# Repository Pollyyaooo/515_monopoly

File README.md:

# Smart Monopoly

A smart Monopoly system that automatically tracks board state and enforces rules, so players can focus on strategy and fun.

## Demo Videos

| Scenario | Link |
|---|---|
| Vision detection — green house | [Watch](https://drive.google.com/file/d/1YYkAQqQGW3G5yaRUnQ6ajyW9RlyFcLrm/view?usp=drive_link) |
| Vision detection — red hotel | [Watch](https://drive.google.com/file/d/1fPO76GP8kFQUbU6NWimg8kV7IUoyudl7/view?usp=drive_link) |
| Auction | [Watch](https://drive.google.com/file/d/1G2KbDcnRxIF2fS2yyap2P3zmI8cTID51/view?usp=drive_link) |
| NFC payment | [Watch](https://drive.google.com/file/d/1PzwGUXprhIAtn__mJcu651hlFBT1dVyA/view?usp=drive_link) |

## System Overview

The system consists of three main components:

- **Vision subsystem** — Grove Vision AI V2 detects house/hotel placement on the board. An ESP32-C3 processes the raw coordinates into property-level data and transmits it to the central bank via ESP-NOW.
- **Central bank** — CrowPanel ESP32 5" manages all public game logic (dice rolls, chance/community cards, auctions, jail) and syncs state to both player devices via BLE. It also receives vision data and alerts players if houses are placed incorrectly.
- **Player devices (×2)** — Each device (XIAO ESP32-S3) has an OLED display, 4 buttons, and an NFC reader. Players use buttons to interact with the game and tap devices together for rent payments and auctions.

## Repository Structure

```
515_monopoly/
├── README.md
├── assets/
│   ├── full_view.jpg
│   └── details.jpg
├── software/
│   ├── README.md               # Code running instructions
│   ├── central_bank/           # CrowPanel ESP32 game logic & display
│   ├── player_card/            # XIAO ESP32-S3 player device firmware
│   ├── vision/                 # Grove Vision AI V2 + ESP32-C3 (ESP-NOW sender)
│   ├── central_display_test/   # Display UI testing
│   └── player_device_test/     # Player device testing
├── hardware/
│   ├── playbox+vision.f3z      # Fusion 360 enclosure & camera mount
│   ├── playbox_lasercut/       # SVG files for laser cutting
│   ├── player_card.f3z         # Fusion 360 player card enclosure
│   ├── player_card_pcb/        # PCB design files
│   ├── player_card_model/      # Player card 3D model files
│   └── vision_archi/           # Vision module hardware files
├── docs/
│   ├── milestone1.pdf
│   ├── milestone2.pdf
│   └── milestone3.pdf
└── test/                       # Early-stage hardware experiments (abandoned)
    ├── RFID test/
    ├── Hall Effect test/
    └── FSR test/
```

## Hardware

| Component | Role |
|---|---|
| Grove Vision AI V2 | House / hotel detection |
| ESP32-C3 | Coordinate processing & ESP-NOW transmission |
| CrowPanel ESP32 5" | Central bank — game logic & public display |
| XIAO ESP32-S3 (×2) | Player devices |
| OLED SSD1351 (×2) | Player display |
| NFC reader (×2) | Rent payment between players |

## Communication

| Link | Protocol |
|---|---|
| Grove Vision AI V2 → ESP32-C3 | UART |
| ESP32-C3 → CrowPanel | ESP-NOW |
| CrowPanel ↔ Player devices | BLE |
| Player device ↔ Player device | NFC |

## Team

- **Sienna** — All software (except vision model training)
- **Polly** — All hardware (enclosure, PCB, player card), vision model training & grid calibration

## Legacy Test Code

The `test/` folder contains early-stage hardware experiments (RFID, Hall Effect, FSR) that were explored during Milestone 1 but later abandoned in favour of the vision-based detection approach.

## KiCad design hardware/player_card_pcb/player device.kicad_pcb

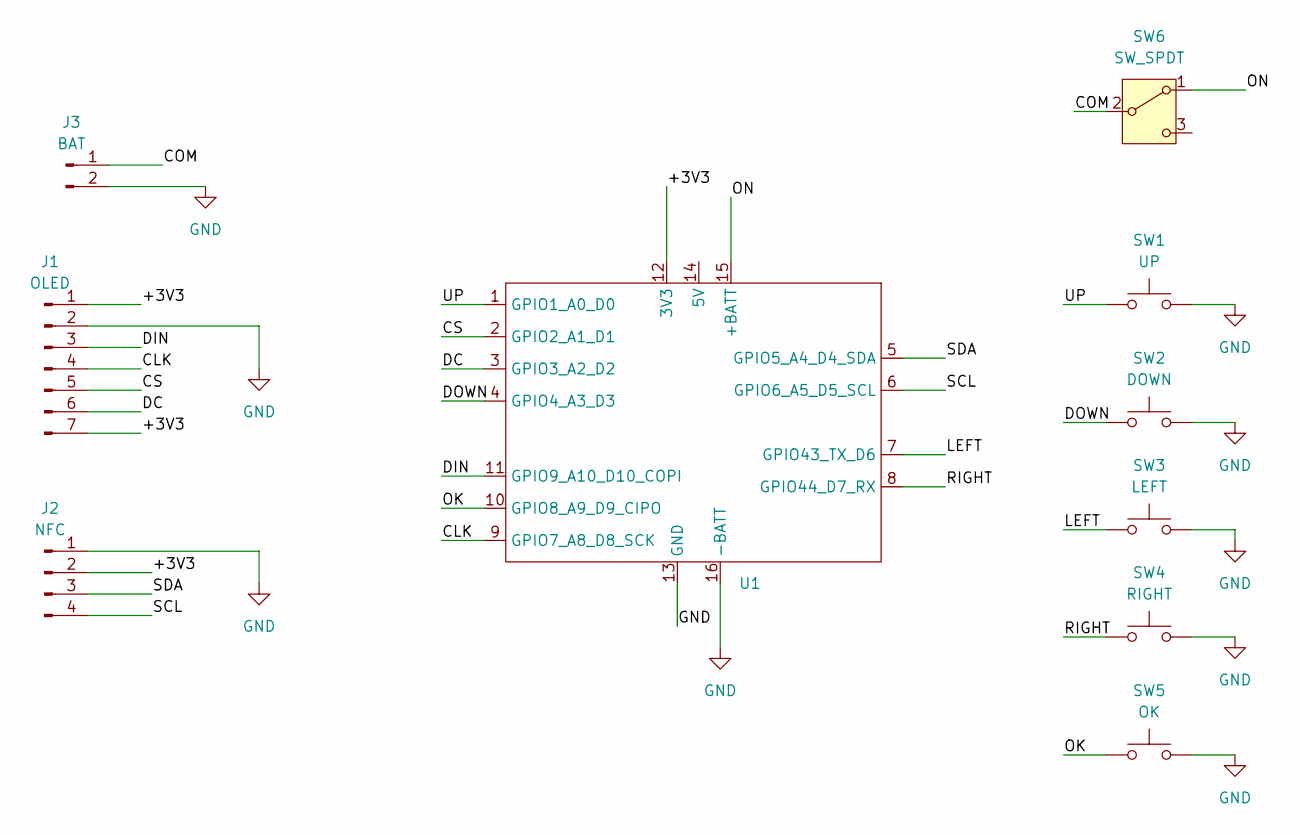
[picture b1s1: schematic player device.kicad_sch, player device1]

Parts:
J1: OLED; PinHeader_1x07_P2.54mm_Vertical
J2: NFC; PinHeader_1x04_P2.54mm_Vertical
J3: BAT; JST_SH_SM02B-SRSS-TB_1x02-1MP_P1.00mm_Horizontal
SW1: UP; SW_TS04-66-70-BK-260-SMT
SW2: DOWN; SW_TS04-66-70-BK-260-SMT
SW3: LEFT; SW_TS04-66-70-BK-260-SMT
SW4: RIGHT; SW_TS04-66-70-BK-260-SMT
SW5: OK; SW_TS04-66-70-BK-260-SMT
SW6: SW_SPDT; PinHeader_1x03_P2.54mm_Vertical
U1: XIAO_ESP32

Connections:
/+3V3: J1.1 (VCC), J1.7 (RST), J2.2 (VCC), U1.12 (3V3)
/CLK: J1.4 (CLK), U1.9 (GPIO7_A8_D8_SCK)
/COM: J3.1 (+), SW6.2 (B)
/CS: J1.5 (CS), U1.2 (GPIO2_A1_D1)
/DC: J1.6 (DC), U1.3 (GPIO3_A2_D2)
/DIN: J1.3 (DIN), U1.11 (GPIO9_A10_D10_COPI)
/DOWN: SW2.1, U1.4 (GPIO4_A3_D3)
/LEFT: SW3.1, U1.7 (GPIO43_TX_D6)
/OK: SW5.1, U1.10 (GPIO8_A9_D9_CIPO)
/ON: SW6.1 (A), U1.15 (+BATT)
/RIGHT: SW4.1, U1.8 (GPIO44_D7_RX)
/SCL: J2.4 (SCL), U1.6 (GPIO6_A5_D5_SCL)
/SDA: J2.3 (SDA), U1.5 (GPIO5_A4_D4_SDA)
/UP: SW1.1, U1.1 (GPIO1_A0_D0)
GND: J1.2 (GND), J2.1 (GND), J3.2 (-), SW1.2, SW2.2, SW3.2, SW4.2, SW5.2, U1.13 (GND), U1.16 (-BATT)

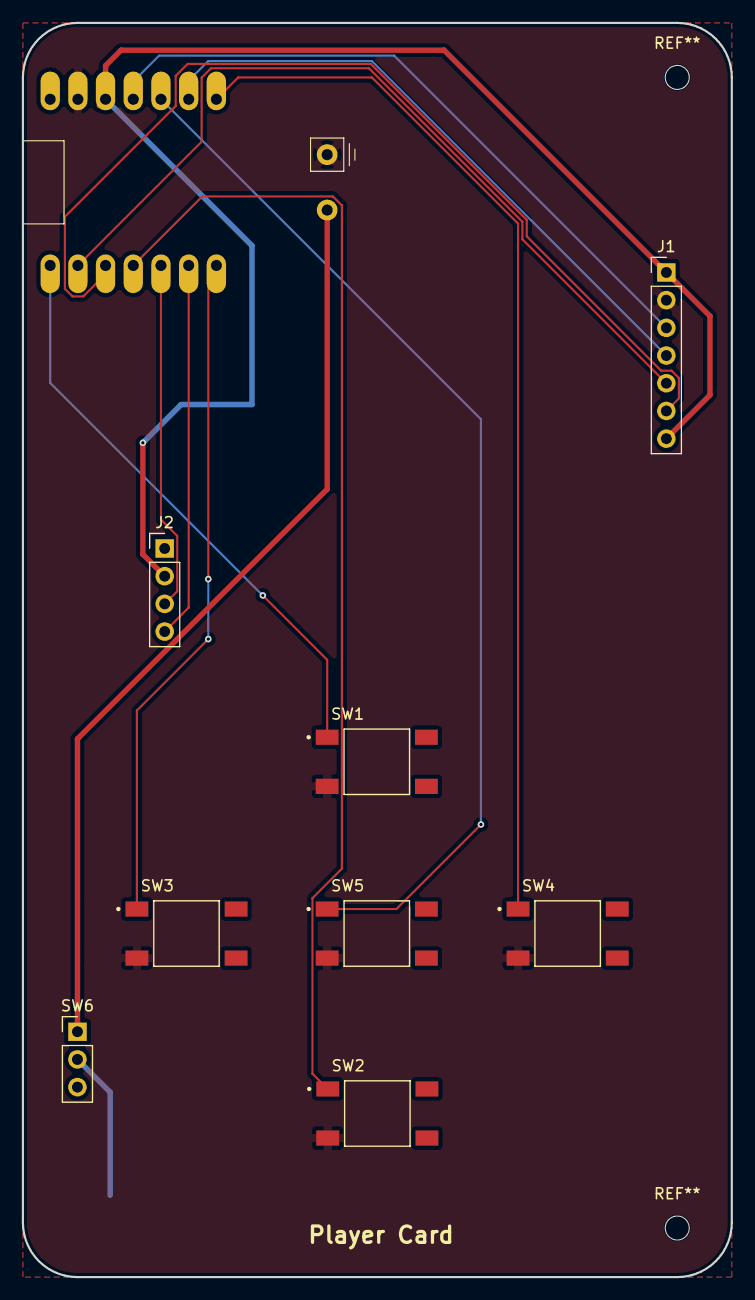
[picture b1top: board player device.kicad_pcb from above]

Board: 2 copper layers, 65.0 x 115.0 mm, 10 parts (1 on the bottom side), 15 nets.

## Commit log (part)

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2026-04-20 update milestone1
2026-04-20 upload milestone2
2026-04-24 vision train 1
2026-04-24 sensing file make
2026-04-24 magnetic add
2026-04-27 hall readme add
2026-06-08 collect
2026-06-08 project finished
